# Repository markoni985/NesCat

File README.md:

# NesCat 0.5

NESCAT by Nathalis
prototype version: 0.5 (c)2020
Enhanced version Nintendo Emulator for ESP32

Requirements: ESP32 WEMOS D1 MINI, ST7789 LCD, MICROSD CARD slot,
PCM5102 I2S AUDIO MODULE, OTHER PARTS...

### FEATURES:

- MicroSD card support
- 240*240 1.3" LCD ST7789 display                  
- Composite TV OUT Video PAL
- I2S AUDIO support PCM5102 module
- PS2 (USB) KEYBOARD support (wireless not work)
- huge NES ROMs up to 512kB (read from FLASH)
- PS4 DualShock BlueTooth Gamepad (experimental)

Only for personal & educational use! 

### DIAGRAM (NEW)

### IMAGES:

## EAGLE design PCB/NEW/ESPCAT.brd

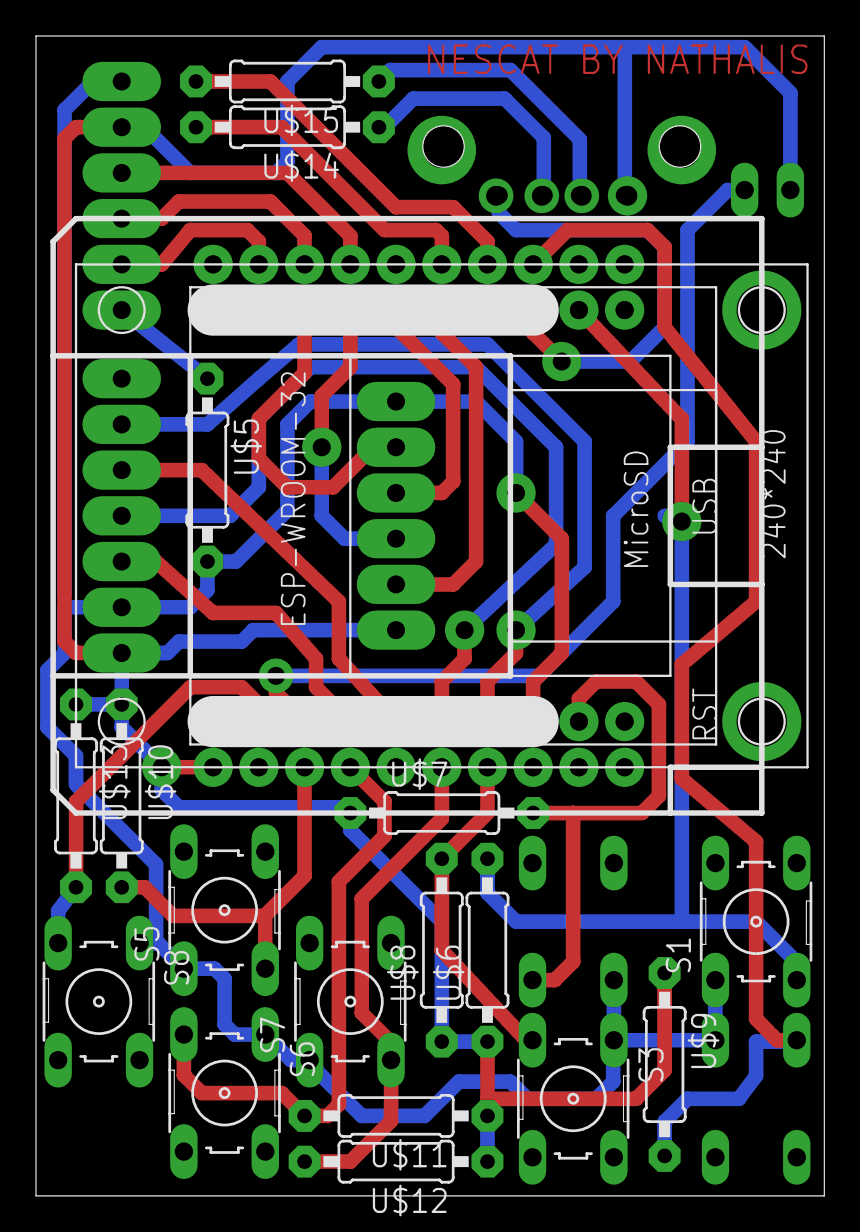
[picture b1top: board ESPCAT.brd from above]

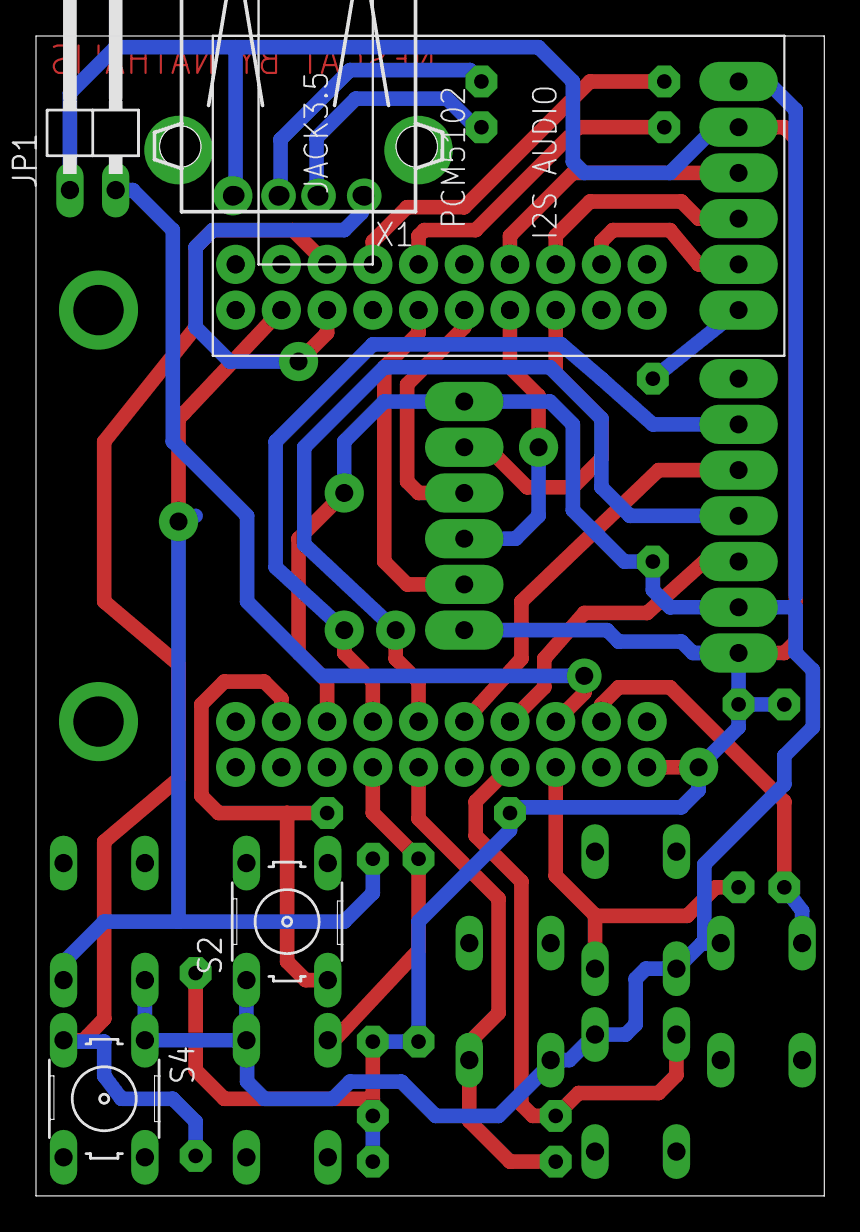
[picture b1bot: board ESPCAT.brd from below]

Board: 2 copper layers, 43.8 x 64.4 mm, 25 parts (5 on the bottom side), 28 nets.

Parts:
JP1: 1X02/90
S1: START; B3F-10XX
S2: SEL; B3F-10XX
S3: B; B3F-10XX
S4: A; B3F-10XX
S5: UP; B3F-10XX
S6: DOWN; B3F-10XX
S7: RIGHT; B3F-10XX
S8: LEFT; B3F-10XX
U$1: WEMOS_D1_MINI_ESP32
U$2: ST7789-1.3INCH
U$3: MICROSD-CARD-MODULE
U$4: I2S-MODULE-PCM5102A-LITE
U$5, U$6, U$7, U$8, U$9, U$10, U$11, U$12, U$13, U$14, U$15: R-0207/10H
X1: USB

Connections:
unnamed: U$1.IO32, U$4.LCK
unnamed: U$4.SCK, U$5.1
unnamed: JP1.2, U$1.IO26
unnamed: U$14.1, X1.2
unnamed: U$15.1, X1.3
unnamed: U$1.VCC, X1.1
unnamed: S4.3, U$1.IO2, U$9.2
unnamed: U$1.IO27, U$4.BCK
unnamed: S1.1, S2.1, S3.1, S4.1, S5.1, S6.1, S7.1, S8.1, U$1.3.3V, U$2.VCC, U$3.3V3, U$4.VIN, U$5.2
unnamed: U$1.IO25, U$4.DIN
unnamed: U$1.IO18, U$2.SCL
unnamed: U$1.IO23, U$2.SDA
unnamed: U$1.IO19, U$2.RES
unnamed: S5.3, U$1.SVN, U$10.2
unnamed: S2.3, U$1.TCK, U$7.2
unnamed: S3.3, U$1.TMS, U$8.2
unnamed: U$1.IO5, U$2.DC
unnamed: U$1.IO22, U$3.CS
unnamed: U$1.IO21, U$3.CLK
unnamed: S6.3, U$1.IO35, U$11.2
unnamed: U$1.IO16, U$3.MISO
unnamed: S1.3, U$1.TD0, U$6.2
unnamed: U$1.IO17, U$3.MOSI
unnamed: U$1.IO4, U$14.2
unnamed: U$1.IO0, U$15.2
unnamed: S8.3, U$1.SVP, U$13.2
unnamed: S7.3, U$1.IO34, U$12.2
unnamed: JP1.1, U$1.GND3, U$2.GND, U$3.GND, U$4.GND, U$6.1, U$7.1, U$8.1, U$9.1, U$10.1, U$11.1, U$12.1, U$13.1, X1.4

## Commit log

2020-10-06 Main
2022-09-19 Fix images
